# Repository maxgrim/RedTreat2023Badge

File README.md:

# RedTreat 2023 badge

- [Software](./Software/redtreat2023/)
- [Hardware](./KiCad/)
- [Presentation](./Presentation.pdf)
- [How to fix](./HOWTOFIX.md)

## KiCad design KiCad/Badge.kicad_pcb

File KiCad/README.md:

# Gerbolyze
```
gerbolyze template production/gerbers --top test.svg
gerbolyze paste production/gerbers test.svg production/gerbers-art
```

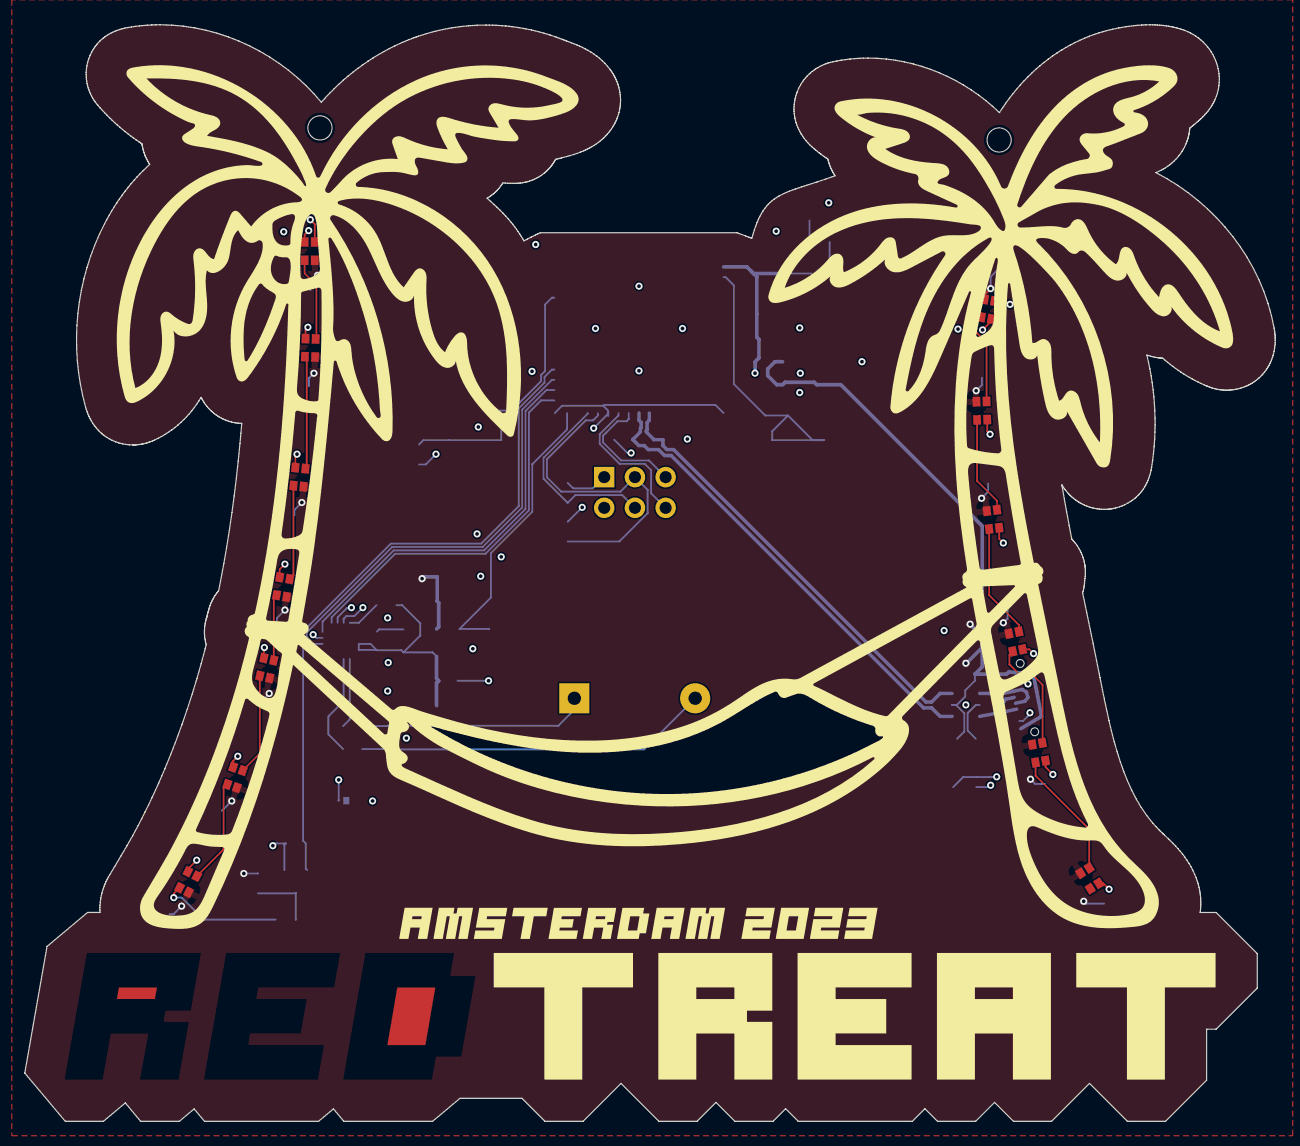
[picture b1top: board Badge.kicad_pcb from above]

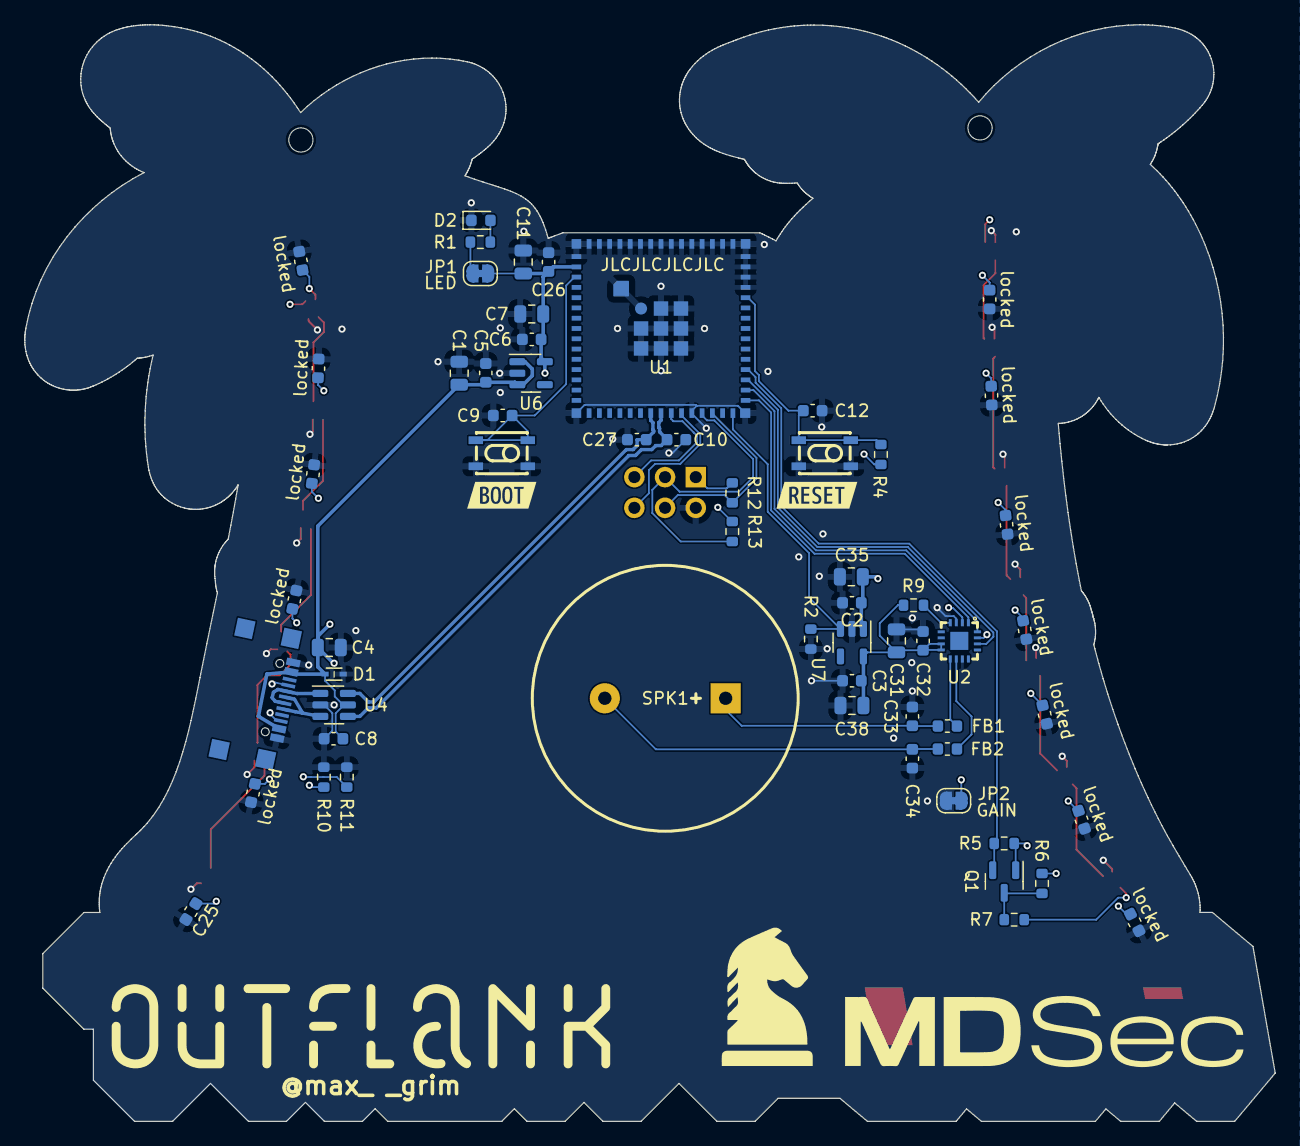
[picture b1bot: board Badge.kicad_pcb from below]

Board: 4 copper layers, 103.5 x 90.7 mm, 78 parts (62 on the bottom side), 43 nets.

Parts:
C1, C4, C7, C11, C31, C35, C38: 10uF; C_0805_2012Metric
C2, C3, C5, C6: 1uF; C_0603_1608Metric
C8, C9, C25, C26, C32: 100nF; C_0603_1608Metric
C10, C27: 22pF; C_0603_1608Metric
C12: locked; C_0603_1608Metric
C33, C34: 220pF; C_0603_1608Metric
D1: LESD5D5.0CT1G; SOD-523_L1.2-W0.8-LS1.6-BI
D2: RED Power; LED_0603_1608Metric
FB1, FB2: PBY160808T-102Y-N; L_0603_1608Metric
J2: SAO; PinSocket_2x03_P2.54mm_Vertical
JP1: PowerLED; SolderJumper-2_P1.3mm_Bridged_RoundedPad1.0x1.5mm
JP2: GAIN; SolderJumper-2_P1.3mm_Bridged_RoundedPad1.0x1.5mm
LED1, LED2, LED3: locked; LED-SMD_4P-L1.6-W1.5_XL-1615RGBC-WS2812B
LED13: WS2812B; LED-SMD_4P-L1.6-W1.5_XL-1615RGBC-WS2812B
Q1: locked; SOT-23
R1, R10, R11: 5.1K; R_0603_1608Metric
R2, R4, R5, R6, R9: 100K; R_0603_1608Metric
R7: 300; R_0603_1608Metric
R12, R13: 3.3K; R_0603_1608Metric
SPK1: GSPK2307P-8R1W; SPK-TH_BD23.0-P10.00-D0.8-L-RD
SW1: BOOT; SW-SMD_4P-L4.2-W3.4-P2.15-LS5.2
SW2: RESET; SW-SMD_4P-L4.2-W3.4-P2.15-LS5.2
U1: ESP32-MINI-1-N4; WIFI-SMD_ESP32-MINI-1-N4
U2: MAX98357AETE+T; TQFN-16_L3.0-W3.0-P0.50-BL-EP1.5
U4: USBLC6-2SC6; SOT-23-6
U6, U7: XC6220B331MR; SOT-23-5
kibuzzard-64FAFBDA: G***; kibuzzard-64FAFBDA
kibuzzard-64FAFBE9: G***; kibuzzard-64FAFBE9
locked: locked; MountingHole_2mm
locked#2, locked#3, locked#4, locked#5, locked#6, locked#7, locked#8, locked#9, locked#11: locked; LED-SMD_4P-L1.6-W1.5_XL-1615RGBC-WS2812B
locked#10: locked; MountingHole_2mm
locked#12, locked#14, locked#15, locked#16, locked#17, locked#18, locked#19, locked#20, locked#21, locked#22, locked#23, locked#24: locked; C_0603_1608Metric
locked#13: MC-107SSY; USB-TYPE-C-SMD_MC-107SSY

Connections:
+3.3V: C6.1, C7.1, C11.1, C26.1, J2.1, JP1.1 (A), Q1.1 (G), R4.1, R5.1, R12.1, R13.1, U1.2 (3V3), U6.5 (VOUT)
+3.3VA: C3.1, C31.1, C32.1, C38.1, R9.1, U2.7 (VDD), U2.8 (VDD), U7.5 (VOUT)
+5V: C1.1, C2.1, C4.1, C5.1, C8.1, C25.1, C35.1, D1.1, LED1.2 (VDD), LED2.2 (VDD), LED3.2 (VDD), LED13.2 (VDD), R6.1, U4.5 (VBUS), U6.1 (VIN), U6.3 (CE), U7.1 (VIN), locked#2.2 (VDD), locked#3.2 (VDD), locked#4.2 (VDD), locked#5.2 (VDD), locked#6.2 (VDD), locked#7.2 (VDD), locked#8.2 (VDD), locked#9.2 (VDD), locked#11.2 (VDD), locked#12.1, locked#13.A4 (VBUS), locked#13.A9 (VBUS), locked#13.B4 (VBUS), locked#13.B9 (VBUS), locked#14.1, locked#15.1, locked#16.1, locked#17.1, locked#18.1, locked#19.1, locked#20.1, locked#21.1, locked#22.1, locked#23.1, locked#24.1
/AU_EN: R2.1, U1.30 (IO36), U7.3 (CE)
/D+: U4.3 (I/O2), locked#13.A6 (D+), locked#13.B6 (D+)
/D-: U4.1 (I/O1), locked#13.A7 (D-), locked#13.B7 (D-)
/ESP_BOOT: C9.2, SW1.1, U1.3 (IO00)
/ESP_EN: C12.2, R4.2, SW2.1, U1.41 (EN)
/I2C_SCL: J2.4, R12.2, U1.28 (IO34)
/I2C_SDA: J2.3, R13.2, U1.27 (IO33)
/I2S_BCK: U1.32 (IO38), U2.16 (BCLK)
/I2S_DATA: U1.31 (IO37), U2.1 (DIN)
/I2S_WS: U1.33 (IO39), U2.14 (LRCLK)
/RGB: Q1.2 (S), R5.2, U1.34 (IO40)
/SAO_IO1: J2.5, U1.24 (IO21)
/SAO_IO2: J2.6, U1.25 (IO26)
/USB_D+: C10.1, U1.23 (USB_D+), U4.4 (I/O2)
/USB_D-: C27.1, U1.22 (USB_D-), U4.6 (I/O1)
GND: C1.2, C2.2, C3.2, C4.2, C5.2, C6.2, C7.2, C8.2, C9.1, C10.2, C11.2, C12.1, C25.2, C26.2, C27.2, C31.2, C32.2, C33.2, C34.2, C35.2, C38.2, D1.2, D2.1 (K), J2.2, JP2.1 (A), LED1.3 (GND), LED2.3 (GND), LED3.3 (GND), LED13.3 (GND), R2.2, R10.2, R11.2, SW1.2, SW2.2, U1.1 (GND), U1.26 (GND), U1.42 (GND), U1.43 (GND), U1.44 (GND), U1.45 (GND), U1.46 (GND), U1.47 (GND), U1.48 (GND), U1.49 (GND), U1.50 (GND), U1.51 (GND), U1.52 (GND), U1.53 (GND), U1.54 (GND), U1.55 (GND), U1.56 (GND), U1.57 (GND), U1.58 (GND), U1.59 (GND), U1.60 (GND), U1.61 (GND), U1.62 (GND), U1.63 (GND), U1.64 (GND), U1.65 (GND), U2.3 (GND), U2.11 (GND), U2.15 (GND), U4.2 (GND), U6.2 (GND), U7.2 (GND), locked#2.3 (GND), locked#3.3 (GND), locked#4.3 (GND), locked#5.3 (GND), locked#6.3 (GND), locked#7.3 (GND), locked#8.3 (GND), locked#9.3 (GND), locked#11.3 (GND), locked#12.2, locked#13.A1 (GND), locked#13.A12 (GND), locked#13.B1 (GND), locked#13.B12 (GND), locked#14.2, locked#15.2, locked#16.2, locked#17.2, locked#18.2, locked#19.2, locked#20.2, locked#21.2, locked#22.2, locked#23.2, locked#24.2
unnamed: D2.2 (A), R1.2
unnamed: JP1.2 (B), R1.1
unnamed: JP2.2 (B), U2.2 (GAIN_SLOT)
unnamed: LED1.4 (DI), R7.1
unnamed: LED1.1 (DO), LED2.4 (DI)
unnamed: LED2.1 (DO), LED3.4 (DI)
unnamed: LED3.1 (DO), locked#6.4 (DI)
unnamed: locked#6.1 (DO), locked#8.4 (DI)
unnamed: locked#3.4 (DI), locked#8.1 (DO)
unnamed: locked#3.1 (DO), locked#4.4 (DI)
unnamed: locked#4.1 (DO), locked#5.4 (DI)
unnamed: locked#5.1 (DO), locked#11.4 (DI)
unnamed: locked#2.4 (DI), locked#11.1 (DO)
unnamed: locked#2.1 (DO), locked#9.4 (DI)
unnamed: locked#7.4 (DI), locked#9.1 (DO)
unnamed: LED13.4 (DI), locked#7.1 (DO)
unnamed: Q1.3 (D), R6.2, R7.2
unnamed: C33.1, FB1.2, SPK1.1 (+)
unnamed: C34.1, FB2.2, SPK1.2 (-)
unnamed: FB2.1, U2.10 (OUTN)
unnamed: FB1.1, U2.9 (OUTP)
unnamed: R9.2, U2.4 (~SD_MODE)
unnamed: R10.1, locked#13.A5 (CC1)
unnamed: R11.1, locked#13.B5 (CC2)

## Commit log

2023-10-16 Added hardware
2023-10-16 Added presentation
2023-10-20 Added HOWTOFIX / pictures
